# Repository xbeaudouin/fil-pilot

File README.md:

# Fil Pilot for Home Assistant

This projet permit you to create and use a fil pilot interface on 
Home Assistant.

Several Directories :

`Arduino/` : The Arduino source code
`kicad/` : The kicard pcb and schematics
`home_assistant/` : Some Home Assistant stuff

# TODO

Finish documentation

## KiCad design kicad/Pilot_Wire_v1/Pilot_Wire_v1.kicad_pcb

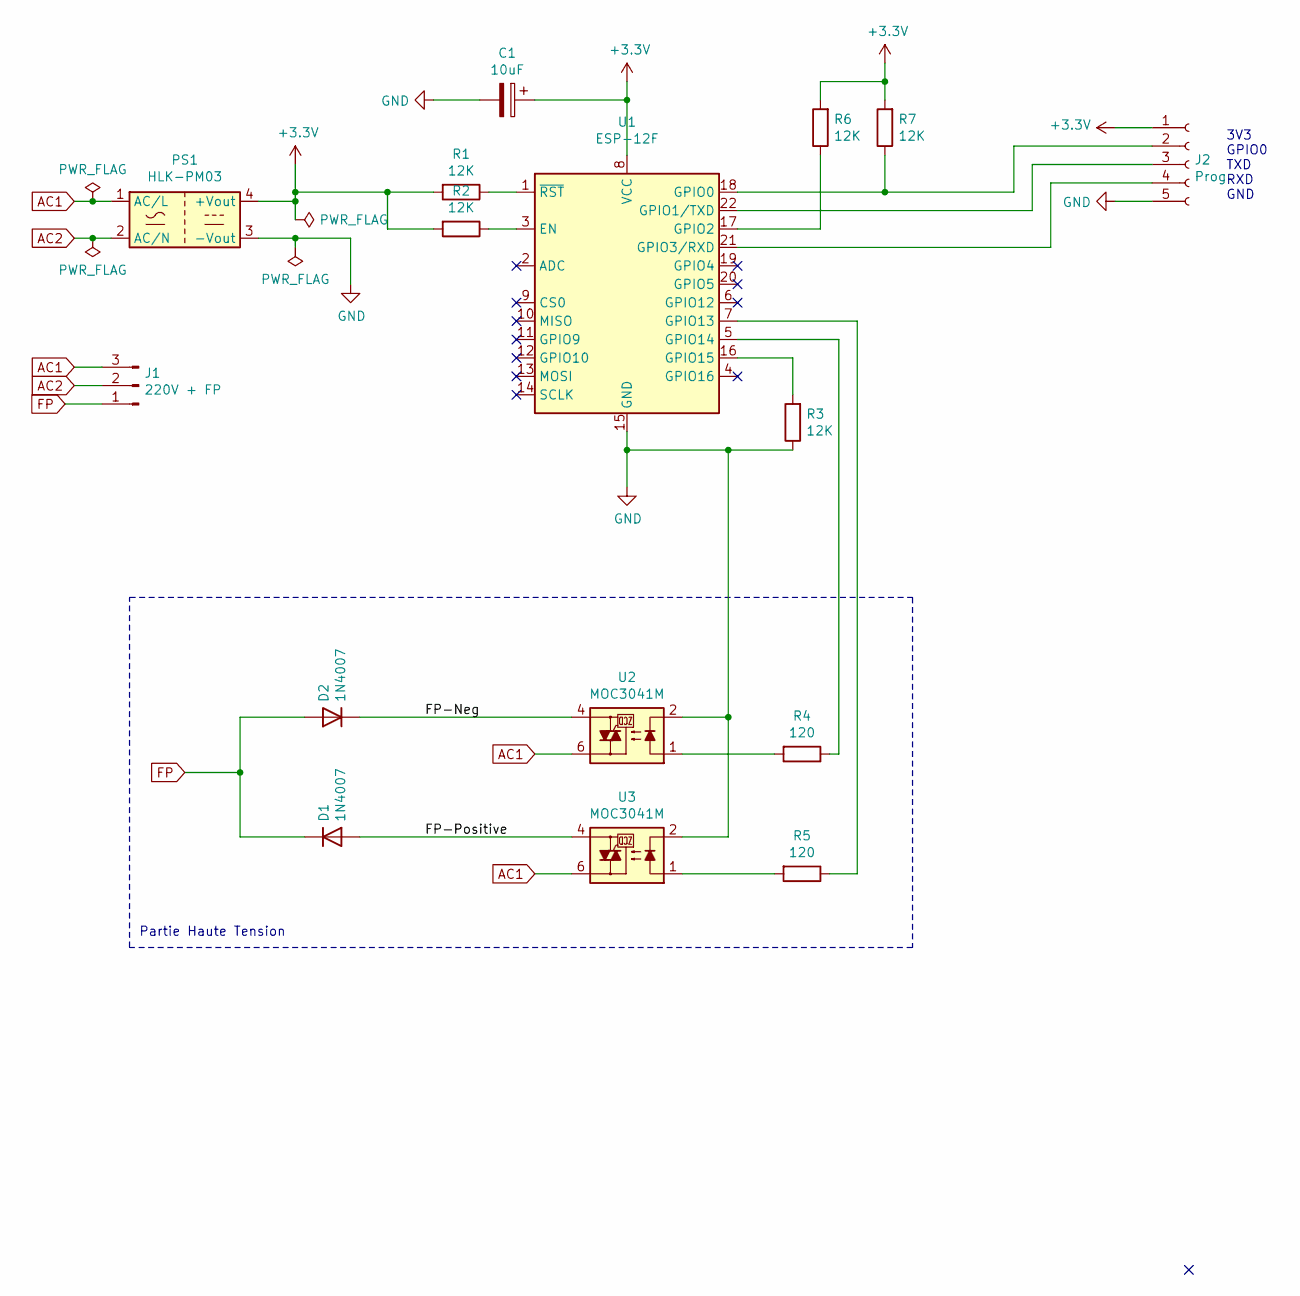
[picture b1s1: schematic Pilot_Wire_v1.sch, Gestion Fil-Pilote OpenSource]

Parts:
C1: 10uF; CP_Radial_D5.0mm_P2.50mm
D1, D2: 1N4007; D_DO-35_SOD27_P7.62mm_Horizontal
J1: 220V + FP; TerminalBlock_Phoenix_MPT-2.54mm_3pol
J2: Prog; Pin_Header_Straight_1x05_Pitch2.54mm
PS1: HLK-PM03
R1, R2, R3, R6, R7: 12K; R_Axial_DIN0204_L3.6mm_D1.6mm_P7.62mm_Horizontal
R4, R5: 120; R_Axial_DIN0204_L3.6mm_D1.6mm_P7.62mm_Horizontal
U1: ESP-12F; ESP-12E
U2, U3: MOC3041M; DIP-6_W7.62mm_LongPads

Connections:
+3V3: C1.1, J2.1, PS1.4 (+Vout), R1.2, R2.2, R6.2, R7.2, U1.8 (VCC)
/FP-Neg: D2.1 (K), U2.4
/FP-Positive: D1.2 (A), U3.4
AC1: J1.3, PS1.1 (AC/L), U2.6, U3.6
AC2: J1.2, PS1.2 (AC/N)
FP: D1.1 (K), D2.2 (A), J1.1
GND: C1.2, J2.5, PS1.3 (-Vout), R3.1, U1.15 (GND), U2.2, U3.2
unnamed: J2.2, R7.1, U1.18 (GPIO0)
unnamed: J2.3, U1.22 (GPIO1/TXD)
unnamed: J2.4, U1.21 (GPIO3/RXD)
unnamed: R1.1, U1.1 (~RST)
unnamed: R2.1, U1.3 (EN)
unnamed: R3.2, U1.16 (GPIO15)
unnamed: R4.1, U1.5 (GPIO14)
unnamed: R4.2, U2.1
unnamed: R5.1, U1.7 (GPIO13)
unnamed: R5.2, U3.1
unnamed: R6.1, U1.17 (GPIO2)

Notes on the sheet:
3V3 GPIO0 TXD RXD GND
Partie Haute Tension

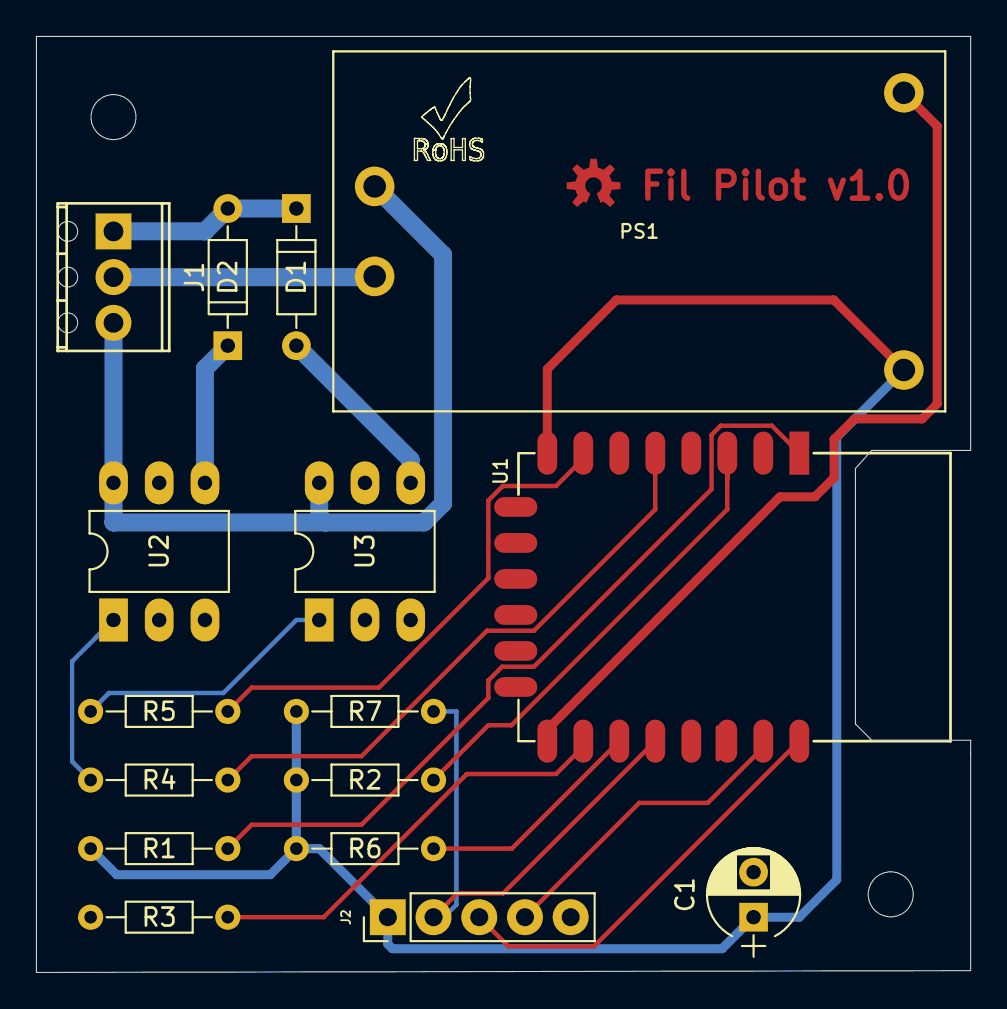
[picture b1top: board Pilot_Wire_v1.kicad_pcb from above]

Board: 2 copper layers, 51.9 x 52.0 mm, 16 parts (0 on the bottom side), 18 nets.

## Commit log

2024-10-09 Initial public public project
2024-10-09 Added Home Assistant Cards
2024-10-09 Added TODO
